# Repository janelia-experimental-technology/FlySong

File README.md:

# FlySong
Song Torrent: A 96 Chamber Fly Courtship Recording Array.

[Preprint](https://www.biorxiv.org/content/10.1101/2024.01.09.574712v1)

The 96 Chamber Array and open-source software was designed to provide high throughput acquisition of Drosophila fly courtship songs. 
Up to 96 separate chambers can be recorded simultaneously along with temperature data for each chamber. Chambers are designed as three 
arrays of 32 chambers each and have sliding partitions to allow loading of separated males and females. The chambers can be top loaded
using a mouth pipette with a sliding cover and loading hole or bottom loaded through a slit in the lower mesh. The latter method could
be used by auto-loading systems. Two optogenetic light drivers are provided and their timing and brightness can be controlled. A camera 
frame trigger ouput is also provided. The software allows any number and arrangement of chambers to be recorded. A separate time and 
brightness comma-separated variable (CSV) file defines the optogenetic light pattern. A separate CSV file can be used to predefine the
individual sample names and their chamber locations, or this information can be entered interactively in the GUI and saved. All data 
and metadata (lights, temperatures, camera triggers, audio, sample information, etc.) are saved to .WAV files

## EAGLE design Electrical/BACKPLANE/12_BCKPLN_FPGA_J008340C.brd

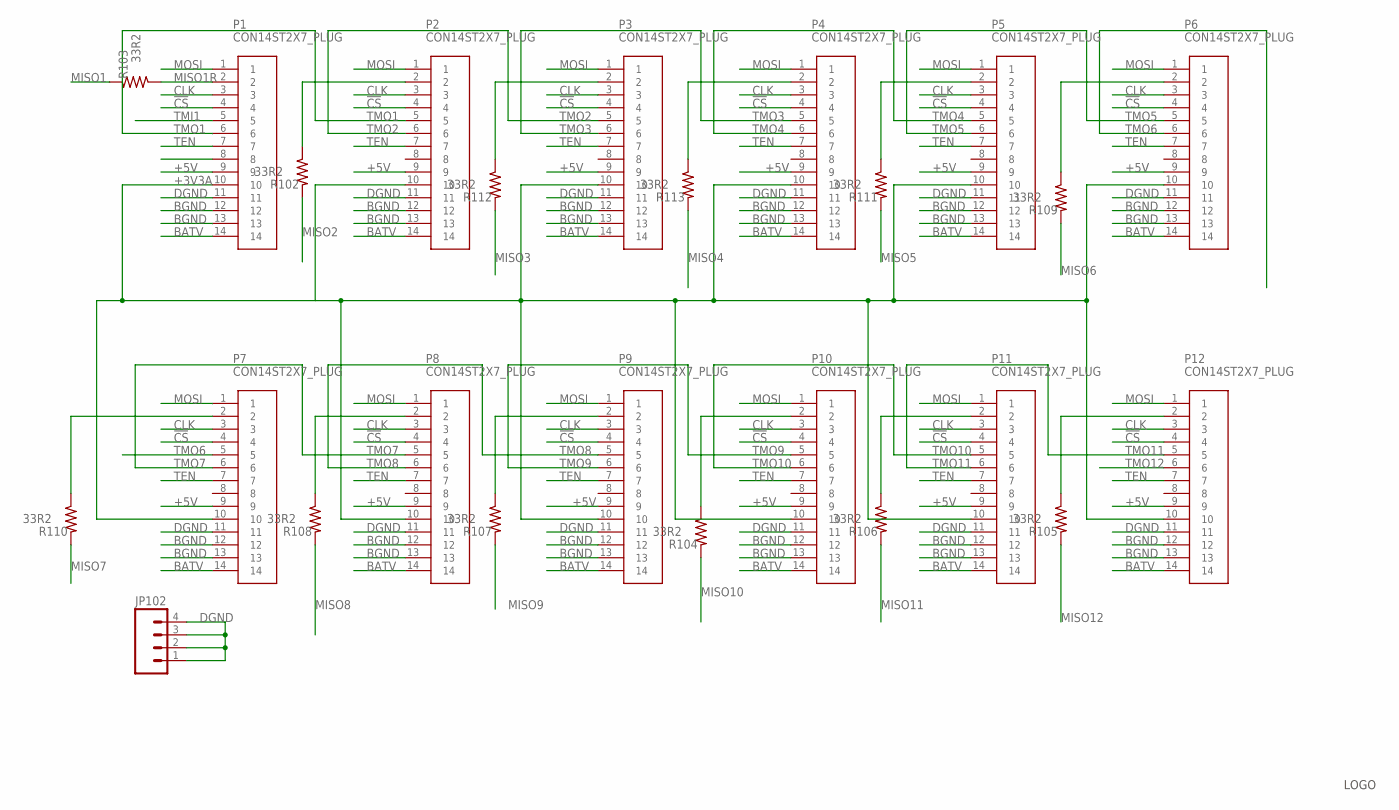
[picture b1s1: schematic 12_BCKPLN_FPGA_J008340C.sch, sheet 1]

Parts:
JP102: M04LOCK; 1X04_LOCK
P1, P2, P3, P4, P5, P6, P7, P8, P9, P10, P11, P12: CON14ST2X7_PLUG; 2X7_PLUG
R102, R103, R104, R105, R106, R107, R108, R109, R110, R111, R112, R113: 33R2; 0805S
U$1: JFRC-LOGOLOGO_OP; LOGO_BMP_OP

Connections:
!CS: P1.4, P2.4, P3.4, P4.4, P5.4, P6.4, P7.4, P8.4, P9.4, P10.4, P11.4, P12.4; also elsewhere on the board
+3V3A: P1.10, P2.10, P3.10, P4.10, P5.10, P6.10, P7.10, P8.10, P9.10, P10.10, P11.10, P12.10; also elsewhere on the board
+5V: P1.9, P2.9, P3.9, P4.9, P5.9, P6.9, P7.9, P8.9, P9.9, P10.9, P11.9, P12.9; also elsewhere on the board
BATV: P1.14, P2.14, P3.14, P4.14, P5.14, P6.14, P7.14, P8.14, P9.14, P10.14, P11.14, P12.14; also elsewhere on the board
BGND: P1.12, P1.13, P2.12, P2.13, P3.12, P3.13, P4.12, P4.13, P5.12, P5.13, P6.12, P6.13, P7.12, P7.13, P8.12, P8.13, P9.12, P9.13, P10.12, P10.13, P11.12, P11.13, P12.12, P12.13; also elsewhere on the board
CLK: P1.3, P2.3, P3.3, P4.3, P5.3, P6.3, P7.3, P8.3, P9.3, P10.3, P11.3, P12.3; also elsewhere on the board
DGND: JP102.1, JP102.2, JP102.3, JP102.4, P1.11, P2.11, P3.11, P4.11, P5.11, P6.11, P7.11, P8.11, P9.11, P10.11, P11.11, P12.11; also elsewhere on the board
MISO1: R103.2; also elsewhere on the board
MISO1R: P1.2, R103.1
MISO2: R102.2; also elsewhere on the board
MISO3: R112.2; also elsewhere on the board
MISO4: R113.2; also elsewhere on the board
MISO5: R111.2; also elsewhere on the board
MISO6: R109.2; also elsewhere on the board
MISO7: R110.2; also elsewhere on the board
MISO8: R108.2; also elsewhere on the board
MISO9: R107.2; also elsewhere on the board
MISO10: R104.2; also elsewhere on the board
MISO11: R106.2; also elsewhere on the board
MISO12: R105.2; also elsewhere on the board
MOSI: P1.1, P2.1, P3.1, P4.1, P5.1, P6.1, P7.1, P8.1, P9.1, P10.1, P11.1, P12.1; also elsewhere on the board
unnamed: P2.2, R102.1
unnamed: P3.2, R112.1
unnamed: P4.2, R113.1
unnamed: P5.2, R111.1
unnamed: P6.2, R109.1
unnamed: P12.2, R105.1
unnamed: P11.2, R106.1
unnamed: P10.2, R104.1
unnamed: P9.2, R107.1
unnamed: P8.2, R108.1
unnamed: P7.2, R110.1
TEN: P1.7, P2.7, P3.7, P4.7, P5.7, P6.7, P7.7, P8.7, P9.7, P10.7, P11.7, P12.7; also elsewhere on the board
TMI1: P1.5; also elsewhere on the board
TMO1: P1.6, P2.5
TMO2: P2.6, P3.5
TMO3: P3.6, P4.5
TMO4: P4.6, P5.5
TMO5: P5.6, P6.5
TMO6: P6.6, P7.5
TMO7: P7.6, P8.5
TMO8: P8.6, P9.5
TMO9: P9.6, P10.5
TMO10: P10.6, P11.5
TMO11: P11.6, P12.5
TMO12: P12.6; also elsewhere on the board

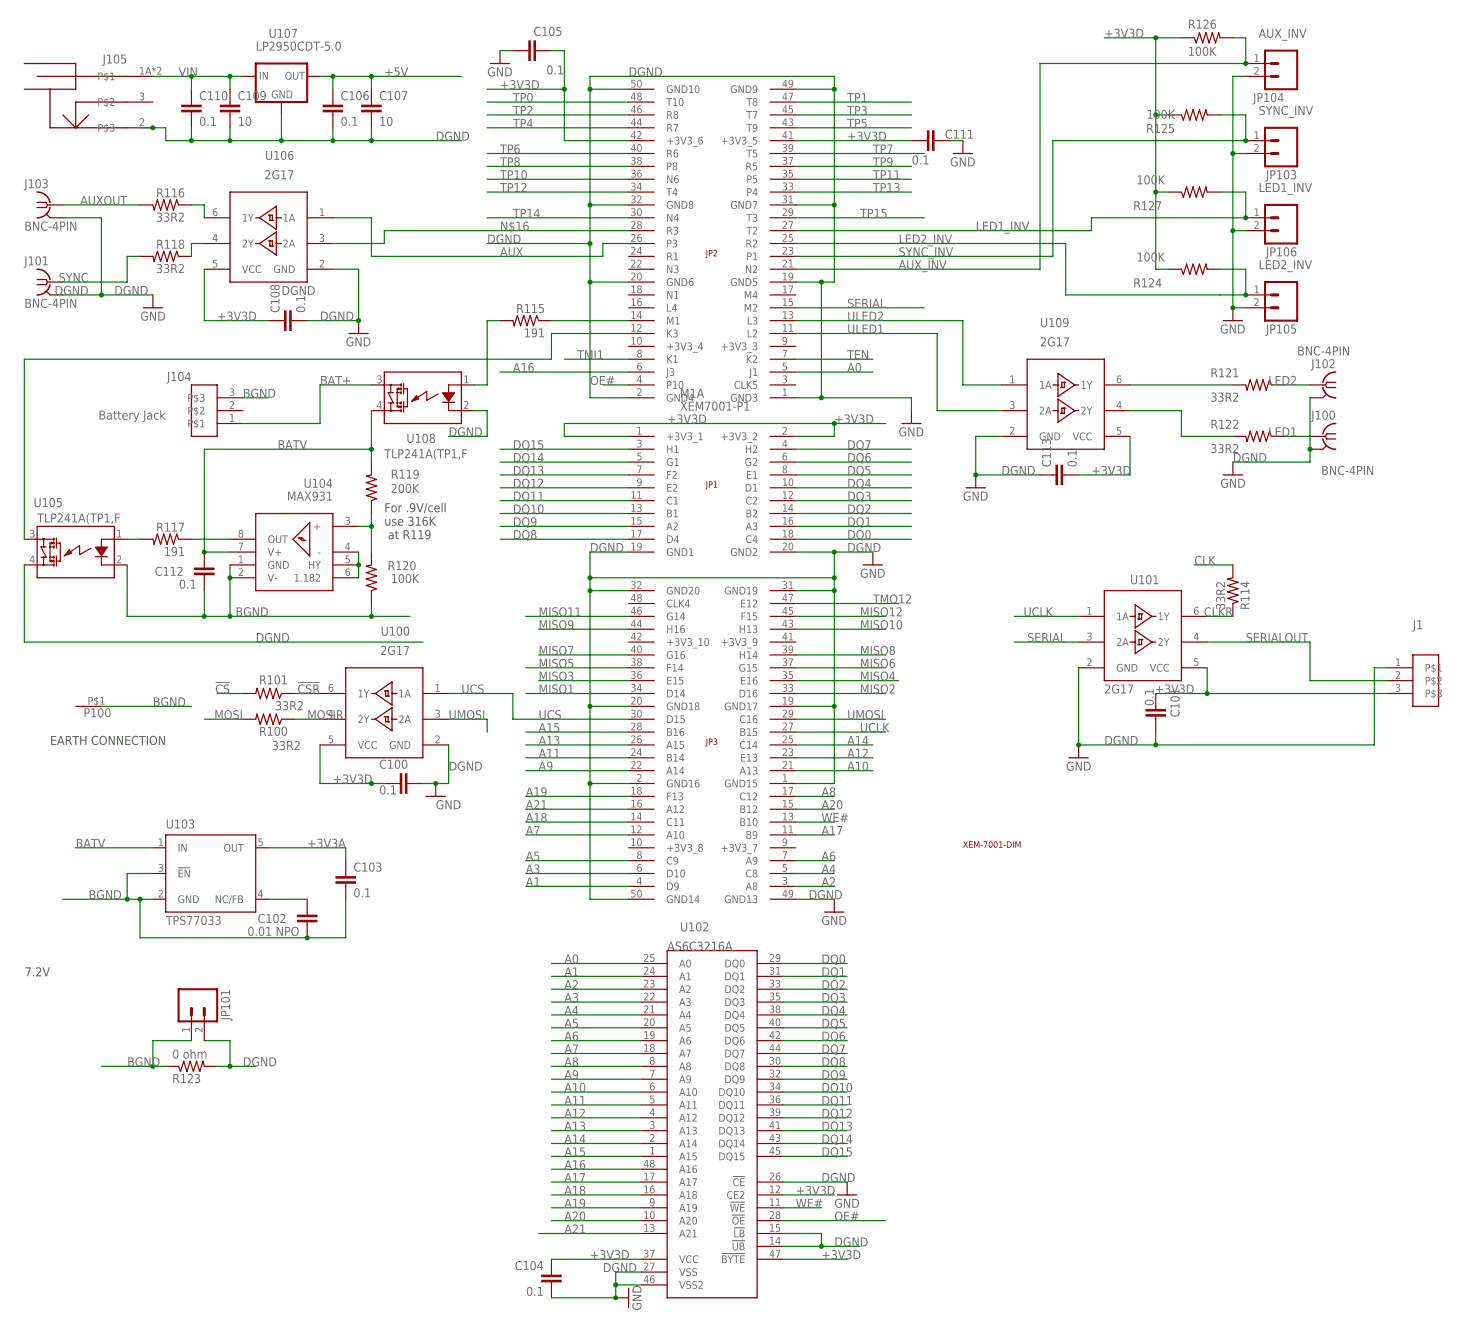
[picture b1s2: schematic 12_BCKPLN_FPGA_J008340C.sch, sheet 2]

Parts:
C100, C101, C103, C104, C105, C106, C108, C110, C111, C112, C113: 0.1; 0603S
C102: 0.01 NPO; 0805S
C107, C109: 10; 1210S
J1: CON3AMPMODU-3; AMPMODU-3
J100, J101, J102, J103: BNC-4PIN
J104: Battery Jack; 975
J105: POWER_JACK_SHUNTPJ-002; PJ-002
JP101, JP103, JP104, JP105, JP106: M02LOCK; 1X02_LOCK
M1: XEM7001-OUTLINE
M1A: XEM7001-P1; 2X10
M1B: XEM7001-P2; 2X25
M1C: XEM7001-P3; 2X25
P100: CON1BANANA-1; BANANA-1
R100, R101, R114, R116, R118, R121, R122: 33R2; 0805S
R115, R117: 191; 0805S
R119: 200K; 0805S
R120, R124, R125, R126, R127: 100K; 0805S
R123: 0 ohm; 0805S
U100, U101, U106, U109: 2G17; SOT23-6
U102: AS6C3216A; TSSOP48-12X20
U103: TPS77033; SOT23-DBV
U104: MAX931; SOIC8
U105, U108: TLP241A(TP1,F; SMD4-GULL
U107: LP2950CDT-5.0; DPACK

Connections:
!CS: R101.2; also elsewhere on the board
!CSR: R101.1, U100.6 (1Y)
+3V3A: C103.1, U103.5 (OUT); also elsewhere on the board
+3V3D: C100.1, C101.1, C104.1, C105.1, C108.1, C111.1, C113.2, J1.3, M1A.1 (+3V3_1), M1A.2 (+3V3_2), M1B.41 (+3V3_5), M1B.42 (+3V3_6), R124.1, R125.1, R126.1, R127.1, U100.5 (VCC), U101.5 (VCC), U102.12 (CE2), U102.37 (VCC), U102.47 (!BYTE), U106.5 (VCC), U109.5 (VCC)
+5V: C106.1, C107.1, U107.3 (OUT); also elsewhere on the board
A0: M1B.5 (J1), U102.25 (A0)
A1: M1C.4 (D9), U102.24 (A1)
A2: M1C.3 (A8), U102.23 (A2)
A3: M1C.6 (D10), U102.22 (A3)
A4: M1C.5 (C8), U102.21 (A4)
A5: M1C.8 (C9), U102.20 (A5)
A6: M1C.7 (A9), U102.19 (A6)
A7: M1C.12 (A10), U102.18 (A7)
A8: M1C.17 (C12), U102.8 (A8)
A9: M1C.22 (A14), U102.7 (A9)
A10: M1C.21 (A13), U102.6 (A10)
A11: M1C.24 (B14), U102.5 (A11)
A12: M1C.23 (E13), U102.4 (A12)
A13: M1C.26 (A15), U102.3 (A13)
A14: M1C.25 (C14), U102.2 (A14)
A15: M1C.28 (B16), U102.1 (A15)
A16: M1B.6 (J3), U102.48 (A16)
A17: M1C.11 (B9), U102.17 (A17)
A18: M1C.14 (C11), U102.16 (A18)
A19: M1C.18 (F13), U102.9 (A19)
A20: M1C.15 (B12), U102.10 (A20)
A21: M1C.16 (A12), U102.13 (A21)
AUX: M1B.26 (P3), U106.1 (1A)
AUXOUT: J103.S (1), R116.2
AUX_INV: JP104.1, M1B.21 (N2), R126.2
BAT+: J104.1, U108.3 (DS1)
BATV: C112.1, R119.2, U103.1 (IN), U104.7 (V+), U108.4 (DS2); also elsewhere on the board
BGND: C102.2, C103.2, C112.2, J104.3, JP101.1, P100.P$1, R120.1, R123.1, U103.2 (GND), U103.3 (!EN), U104.1 (GND), U104.2 (V-), U105.2 (K); also elsewhere on the board
CLK: R114.2; also elsewhere on the board
CLKR: R114.1, U101.6 (1Y)
DGND: C100.2, C101.2, C104.2, C105.2, C106.2, C107.2, C108.2, C109.2, C110.2, C111.2, C113.1, J1.1, J100.G1 (GND), J100.G2 (GND), J100.G3 (GND), J100.G4 (GND), J101.G1 (GND), J101.G2 (GND), J101.G3 (GND), J101.G4 (GND), J102.G1 (GND), J102.G2 (GND), J102.G3 (GND), J102.G4 (GND), J103.G1 (GND), J103.G2 (GND), J103.G3 (GND), J103.G4 (GND), J105.2, JP101.2, JP103.2, JP104.2, JP105.2, JP106.2, M1A.19 (GND1), M1A.20 (GND2), M1B.1 (GND3), M1B.2 (GND4), M1B.19 (GND5), M1B.20 (GND6), M1B.31 (GND7), M1B.32 (GND8), M1B.49 (GND9), M1B.50 (GND10), M1C.1 (GND15), M1C.2 (GND16), M1C.19 (GND17), M1C.20 (GND18), M1C.31 (GND19), M1C.32 (GND20), M1C.49 (GND13), M1C.50 (GND14), R123.2, U100.2 (GND), U101.2 (GND), U102.14 (!UB), U102.15 (!LB), U102.26 (!CE), U102.27 (VSS), U102.46 (VSS2), U105.4 (DS2), U106.2 (GND), U107.4 (GND), U108.2 (K), U109.2 (GND); also elsewhere on the board
DQ0: M1A.18 (C4), U102.29 (DQ0)
DQ1: M1A.16 (A3), U102.31 (DQ1)
DQ2: M1A.14 (B2), U102.33 (DQ2)
DQ3: M1A.12 (C2), U102.35 (DQ3)
DQ4: M1A.10 (D1), U102.38 (DQ4)
DQ5: M1A.8 (E1), U102.40 (DQ5)
DQ6: M1A.6 (G2), U102.42 (DQ6)
DQ7: M1A.4 (H2), U102.44 (DQ7)
DQ8: M1A.17 (D4), U102.30 (DQ8)
DQ9: M1A.15 (A2), U102.32 (DQ9)
DQ10: M1A.13 (B1), U102.34 (DQ10)
DQ11: M1A.11 (C1), U102.36 (DQ11)
DQ12: M1A.9 (E2), U102.39 (DQ12)
DQ13: M1A.7 (F2), U102.41 (DQ13)
DQ14: M1A.5 (G1), U102.43 (DQ14)
DQ15: M1A.3 (H1), U102.45 (DQ15)
LED1: J100.S (1), R122.1
LED1_INV: JP106.1, M1B.27 (T2), R127.2
LED2: J102.S (1), R121.1
LED2_INV: JP105.1, M1B.25 (R2), R124.2
MISO1: M1C.34 (D14); also elsewhere on the board
MISO2: M1C.33 (D16); also elsewhere on the board
MISO3: M1C.36 (E15); also elsewhere on the board
MISO4: M1C.35 (E16); also elsewhere on the board
MISO5: M1C.38 (F14); also elsewhere on the board
MISO6: M1C.37 (G15); also elsewhere on the board
MISO7: M1C.40 (G16); also elsewhere on the board
MISO8: M1C.39 (H14); also elsewhere on the board
MISO9: M1C.44 (H16); also elsewhere on the board
MISO10: M1C.43 (H13); also elsewhere on the board
MISO11: M1C.46 (G14); also elsewhere on the board
MISO12: M1C.45 (F15); also elsewhere on the board
MOSI: R100.2; also elsewhere on the board
MOSIR: R100.1, U100.4 (2Y)
unnamed: R117.2, U105.1 (A)
unnamed: R121.2, U109.6 (1Y)
unnamed: R115.2, U108.1 (A)
unnamed: M1B.14 (M1), R115.1
unnamed: C102.1, U103.4 (NC/FB)
unnamed: R117.1, U104.8 (OUT)
unnamed: M1B.28 (R3), U106.3 (2A)
unnamed: R119.1, R120.2, U104.3 (+)
unnamed: R116.1, U106.6 (1Y)
unnamed: R118.1, U106.4 (2Y)
unnamed: R122.2, U109.4 (2Y)
OE#: M1B.4 (P10), U102.28 (!OE)
REF: U104.4 (-), U104.5 (HY), U104.6 (1.182)
SERIAL: M1B.15 (M2), U101.3 (2A)
SERIALOUT: J1.2, U101.4 (2Y)
SYNC: J101.S (1), R118.2
SYNC_INV: JP103.1, M1B.23 (P1), R125.2
TEN: M1B.7 (K2); also elsewhere on the board
TMI1: M1B.8 (K1); also elsewhere on the board
TMO12: M1C.47 (E12); also elsewhere on the board
TP0: M1B.48 (T10)
TP1: M1B.47 (T8)
TP2: M1B.46 (R8)
TP3: M1B.45 (T7)
TP4: M1B.44 (R7)
TP5: M1B.43 (T9)
TP6: M1B.40 (R6)
TP7: M1B.39 (T5)
TP8: M1B.38 (P8)
TP9: M1B.37 (R5)
TP10: M1B.36 (N6)
TP11: M1B.35 (P5)
TP12: M1B.34 (T4)
TP13: M1B.33 (P4)
TP14: M1B.30 (N4)
TP15: M1B.29 (T3)
UCLK: M1C.27 (B15), U101.1 (1A)
UCS: M1C.30 (D15), U100.1 (1A)
ULED1: M1B.11 (L2), U109.3 (2A)
ULED2: M1B.13 (L3), U109.1 (1A)
UMOSI: M1C.29 (C16), U100.3 (2A)
VCHECK: M1B.12 (K3), U105.3 (DS1)
VIN: C109.1, C110.1, J105.1A, J105.1B, U107.1 (IN)
WE#: M1C.13 (B10), U102.11 (!WE)

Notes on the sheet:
7.2V
EARTH CONNECTION
For .9V/cell use 316K at R119

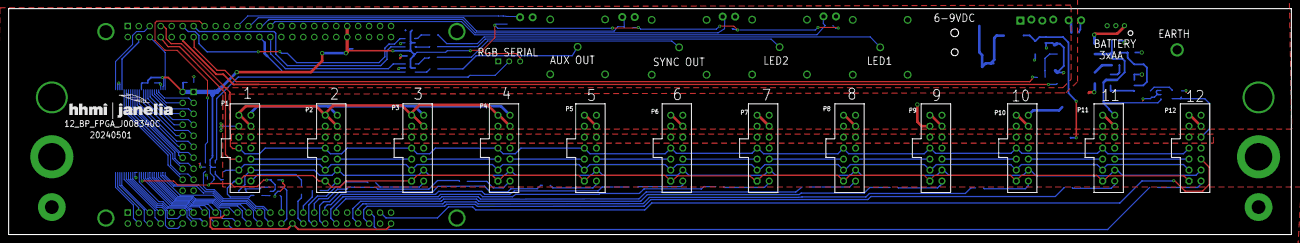
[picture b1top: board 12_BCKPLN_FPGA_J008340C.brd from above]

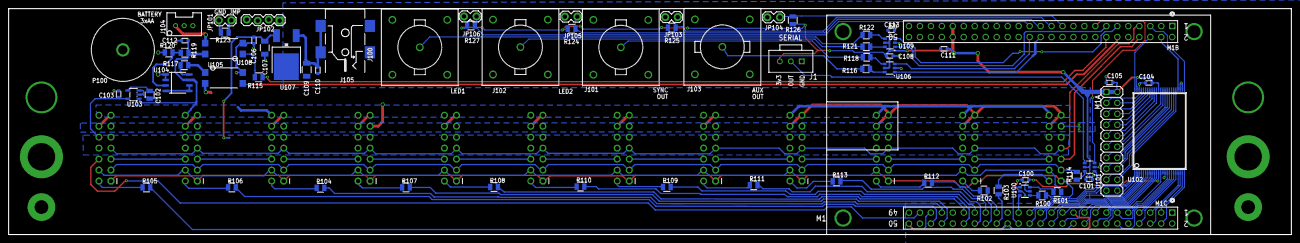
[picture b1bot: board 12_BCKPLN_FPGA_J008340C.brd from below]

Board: 2 copper layers, 297.0 x 52.3 mm, 83 parts (70 on the bottom side), 121 nets.

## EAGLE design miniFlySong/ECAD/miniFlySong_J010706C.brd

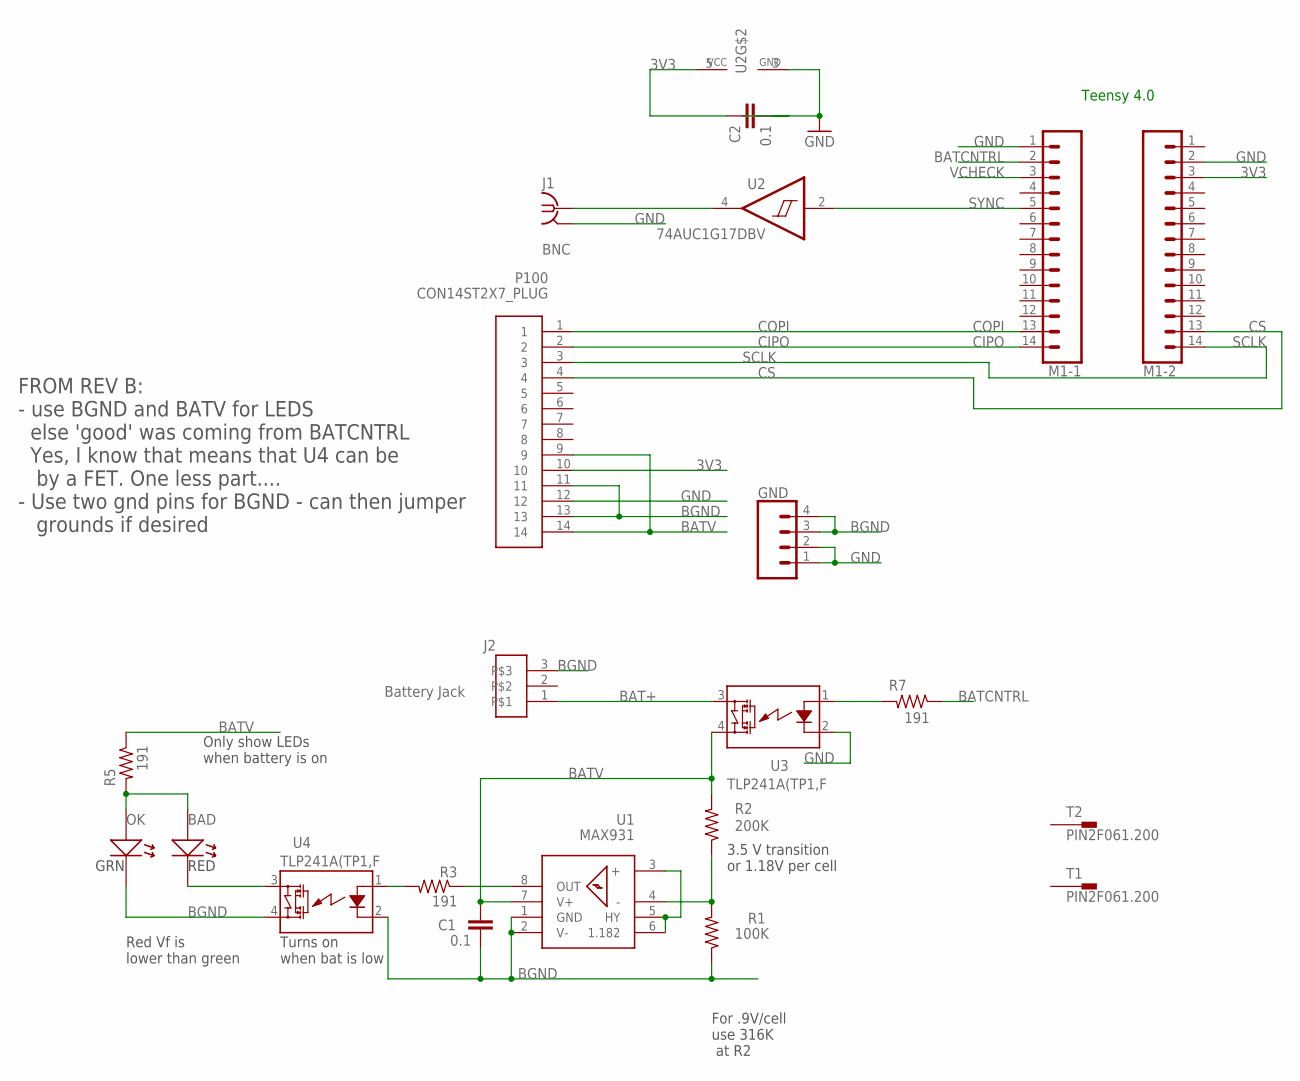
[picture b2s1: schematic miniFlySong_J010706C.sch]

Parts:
BAD: LED4045; LED_SIDE_SHF4045
C1, C2: 0.1; 0603S
GND: CONN_04LOCK; 1X04_LOCK
J1: BNC; BNC-VERT
J2: Battery Jack; 975
M1-1, M1-2: CONN_14; 1X14
OK: LED4045; LED_SIDE_SHF4045
P100: CON14ST2X7_PLUG; 2X7_PLUG
R1: 100K; 0805S
R2: 200K; 0805S
R3, R5, R7: 191; 0805S
T1, T2: PIN2F061.200; F061.200
U1: MAX931; SOIC8
U2: 74AUC1G17DBV; SOT23-5
U3, U4: TLP241A(TP1,F; SMD4-GULL

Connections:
3V3: C2.1, M1-2.3, P100.10, U2.5 (VCC)
BAT+: J2.1, U3.3 (DS1)
BATCNTRL: M1-1.2, R7.1
BATV: C1.1, P100.9, P100.14, R2.2, R5.1, U1.7 (V+), U3.4 (DS2)
BGND: C1.2, GND.3, GND.4, J2.3, OK.C (K), P100.11, P100.13, R1.1, U1.1 (GND), U1.2 (V-), U4.2 (K), U4.4 (DS2)
CIPO: M1-1.14, P100.2
COPI: M1-1.13, P100.1
CS: M1-2.13, P100.4
GND: C2.2, GND.1, GND.2, J1.2 (GND), M1-1.1, M1-2.2, P100.12, U2.3 (GND), U3.2 (K)
unnamed: J1.1, U2.4 (O)
unnamed: BAD.A, OK.A, R5.2
unnamed: BAD.C (K), U4.3 (DS1)
unnamed: R3.2, U4.1 (A)
unnamed: R7.2, U3.1 (A)
unnamed: R3.1, U1.8 (OUT)
unnamed: R1.2, R2.1, U1.4 (-)
REF: U1.3 (+), U1.5 (HY), U1.6 (1.182)
SCLK: M1-2.14, P100.3
SYNC: M1-1.5, U2.2 (I)
VCHECK: M1-1.3

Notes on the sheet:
For .9V/cell use 316K at R2
RED
GRN
3.5 V transition or 1.18V per cell
Turns on when bat is low
Red Vf is lower than green
Only show LEDs when battery is on
FROM REV B: - use BGND and BATV for LEDS else 'good' was coming from BATCNTRL Yes, I know that means that U4 can be by a FET. One less part.... - Use two gnd pins for BGND - can then jumper grounds if desired
Teensy 4.0

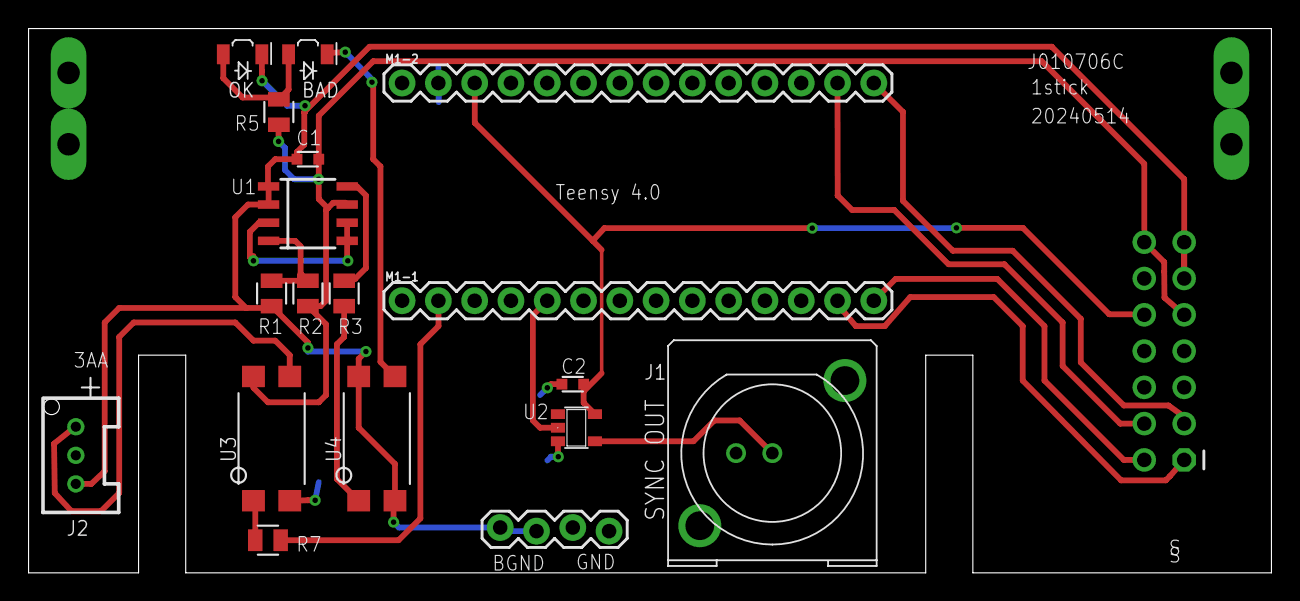
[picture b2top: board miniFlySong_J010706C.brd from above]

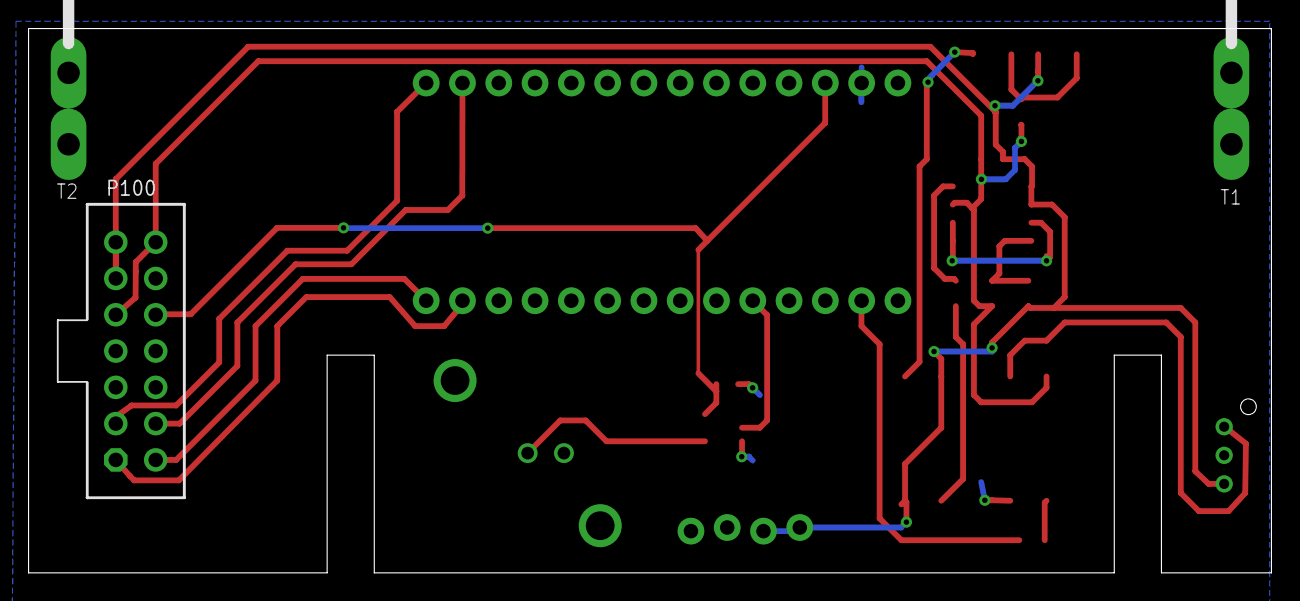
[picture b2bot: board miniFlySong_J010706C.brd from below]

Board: 2 copper layers, 87.0 x 38.1 mm, 21 parts (3 on the bottom side), 19 nets.

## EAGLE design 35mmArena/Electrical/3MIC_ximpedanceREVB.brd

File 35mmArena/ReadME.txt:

35mmArena

The 35mm Arena provides a circular, 35mm diameter, fly arena with recording capbilities. Seven microphones provide coverage for the entire arena. The circuitry is the same design used in the 96 channel FlySong rig, so one 35mm arena can be plugged into one of the 96 channel backplane connectors and use the same software to record audio.

Boards available at Circuithub:

3MIC_backplaneREVA
3MIC_ximpedanceREVB

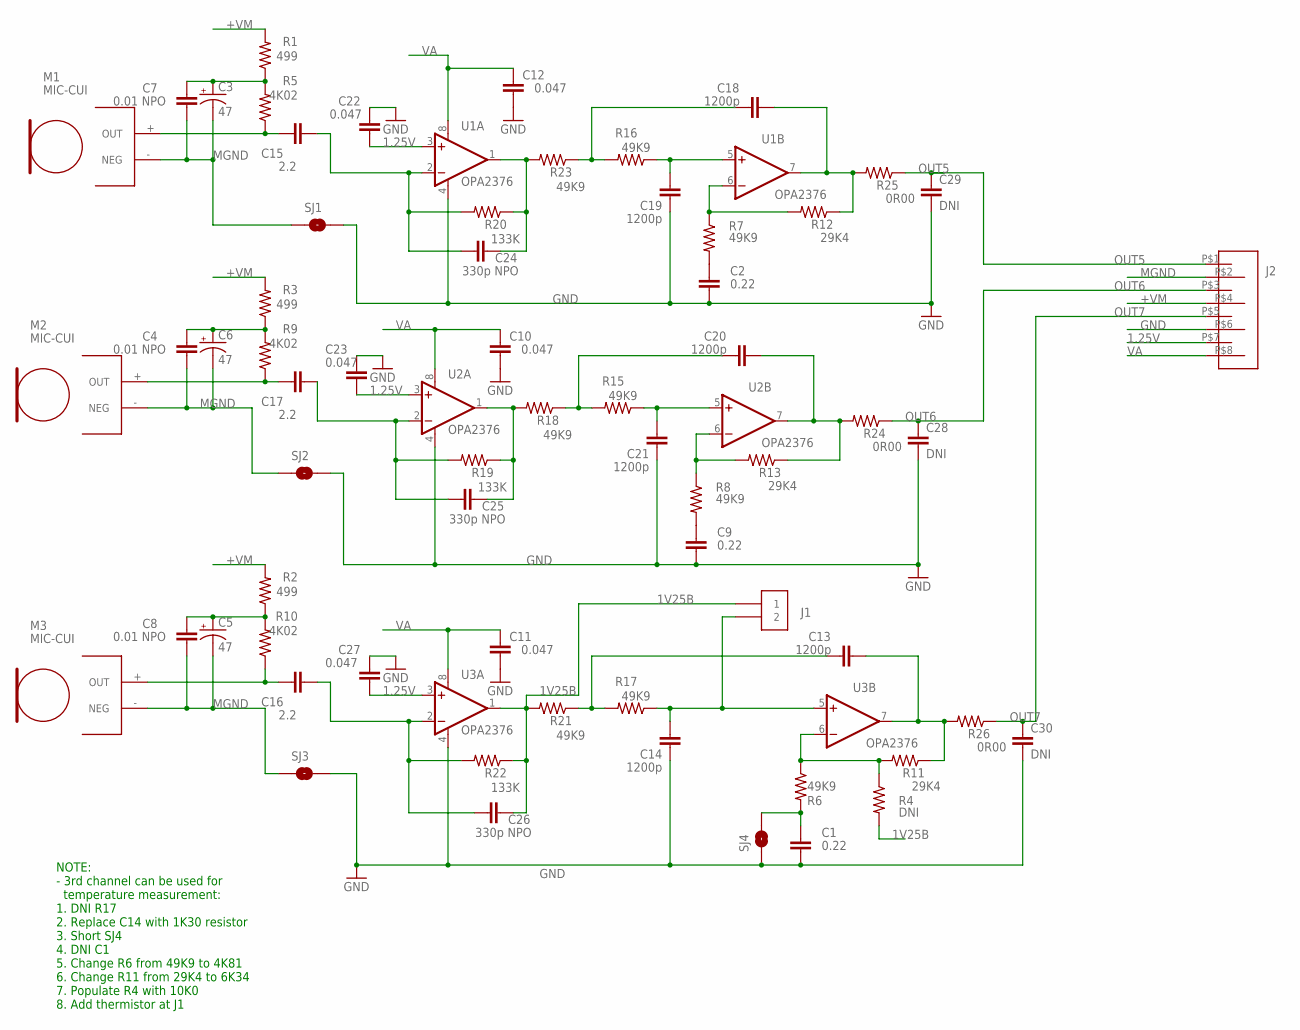
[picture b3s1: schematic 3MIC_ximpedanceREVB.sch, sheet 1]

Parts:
C1, C2, C9: 0.22; 1206S
C3, C5, C6: 47; EIA3216
C4, C7, C8: 0.01 NPO; 0603S
C10, C11, C12, C22, C23, C27: 0.047; 0805S
C13, C14, C18, C19, C20, C21: 1200p; 1206S
C15, C16, C17: 2.2; 1210S
C24, C25, C26: 330p NPO; 0805S
C28, C29, C30: DNI; 0603S
J1: CON2TIP-BOT-PADS; TOP-BOT-PADS
J2: CON8; CON8-EDGE
M1, M2, M3: MIC-CUI; CUI_EDGE
R1, R2, R3: 499; 0603S
R4: DNI; 0603S
R5, R9, R10: 4K02; 0603S
R6, R7, R8, R15, R16, R17, R18, R21, R23: 49K9; 0603S
R11, R12, R13: 29K4; 0603S
R19, R20, R22: 133K; 0603S
R24, R25, R26: 0R00; 0603S
SJ1, SJ2, SJ3: SOLDERJUMPERTRACE; SJ_2S-TRACE
SJ4: SOLDERJUMPERNO; SJ_2S-NO
U1, U2, U3: OPA2376; MSOP08

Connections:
1.25V: C22.2, C23.2, C27.2, J2.P$7 (7), U1.3 (+IN), U2.3 (+IN), U3.3 (+IN)
1V25B: C26.1, J1.1, R4.2, R21.2, R22.1, U3.1 (OUT)
+VM: J2.P$4 (4), R1.2, R2.2, R3.2
GND: C1.1, C2.1, C9.1, C10.1, C11.1, C12.1, C14.1, C19.1, C21.1, C22.1, C23.1, C27.1, C28.2, C29.2, C30.2, J2.P$6 (6), SJ1.2, SJ2.2, SJ3.2, SJ4.1, U1.4 (V-), U2.4 (V-), U3.4 (V-)
M5: C18.1, R12.1, R25.2, U1.7 (OUT)
M6: C20.1, R13.1, R24.2, U2.7 (OUT)
M7: C13.1, R11.1, R26.2, U3.7 (OUT)
MGND: C3.C (-), C4.2, C5.C (-), C6.C (-), C7.2, C8.2, J2.P$2 (2), M1.- (NEG), M2.- (NEG), M3.- (NEG), SJ1.1, SJ2.1, SJ3.1
unnamed: C4.1, C6.A (+), R3.1, R9.2
unnamed: C5.A (+), C8.1, R2.1, R10.2
unnamed: C3.A (+), C7.1, R1.1, R5.2
unnamed: C15.2, C24.2, R20.2, U1.2 (-IN)
unnamed: C24.1, R20.1, R23.2, U1.1 (OUT)
unnamed: C18.2, R16.2, R23.1
unnamed: C19.2, R16.1, U1.5 (+IN)
unnamed: C2.2, R7.2
unnamed: R7.1, R12.2, U1.6 (-IN)
unnamed: C17.1, M2.+ (OUT), R9.1
unnamed: C17.2, C25.2, R19.2, U2.2 (-IN)
unnamed: C25.1, R18.2, R19.1, U2.1 (OUT)
unnamed: C20.2, R15.2, R18.1
unnamed: C21.2, R15.1, U2.5 (+IN)
unnamed: C9.2, R8.2
unnamed: R8.1, R13.2, U2.6 (-IN)
unnamed: C16.1, M3.+ (OUT), R10.1
unnamed: C16.2, C26.2, R22.2, U3.2 (-IN)
unnamed: C13.2, R17.2, R21.1
unnamed: C14.2, J1.2, R17.1, U3.5 (+IN)
unnamed: C1.2, R6.2, SJ4.2
unnamed: R4.1, R6.1, R11.2, U3.6 (-IN)
unnamed: C15.1, M1.+ (OUT), R5.1
OUT5: C29.1, J2.P$1 (1), R25.1
OUT6: C28.1, J2.P$3 (3), R24.1
OUT7: C30.1, J2.P$5 (5), R26.1
VA: C10.2, C11.2, C12.2, J2.P$8 (8), U1.8 (V+), U2.8 (V+), U3.8 (V+)

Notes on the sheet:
NOTE: - 3rd channel can be used for temperature measurement: 1. DNI R17 2. Replace C14 with 1K30 resistor 3. Short SJ4 4. DNI C1 5. Change R6 from 49K9 to 4K81 6. Change R11 from 29K4 to 6K34 7. Populate R4 with 10K0 8. Add thermistor at J1

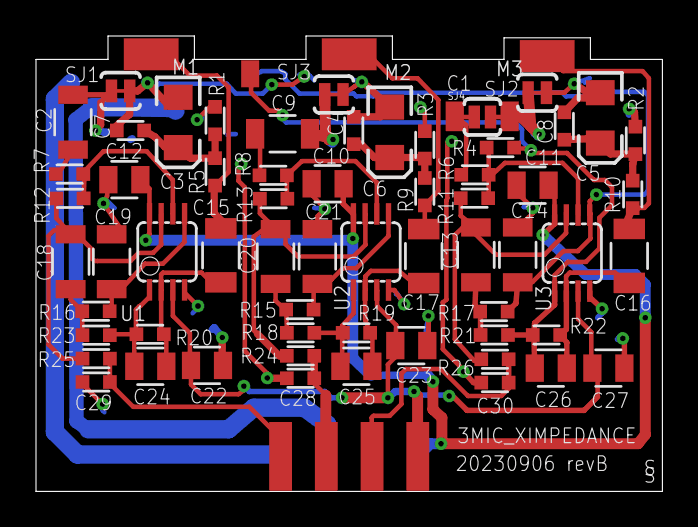
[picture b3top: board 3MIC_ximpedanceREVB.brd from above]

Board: 2 copper layers, 34.8 x 25.3 mm, 67 parts (0 on the bottom side), 35 nets.

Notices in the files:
parts and their libraries:
SparkFun: Licensing: CC v3.0 Share-Alike You are welcome to use this library for commercial purposes.
SparkFun-Connectors: Licensing: Creative Commons ShareAlike 4.0 International - https://creativecommons.org/licenses/by-sa/4.0
